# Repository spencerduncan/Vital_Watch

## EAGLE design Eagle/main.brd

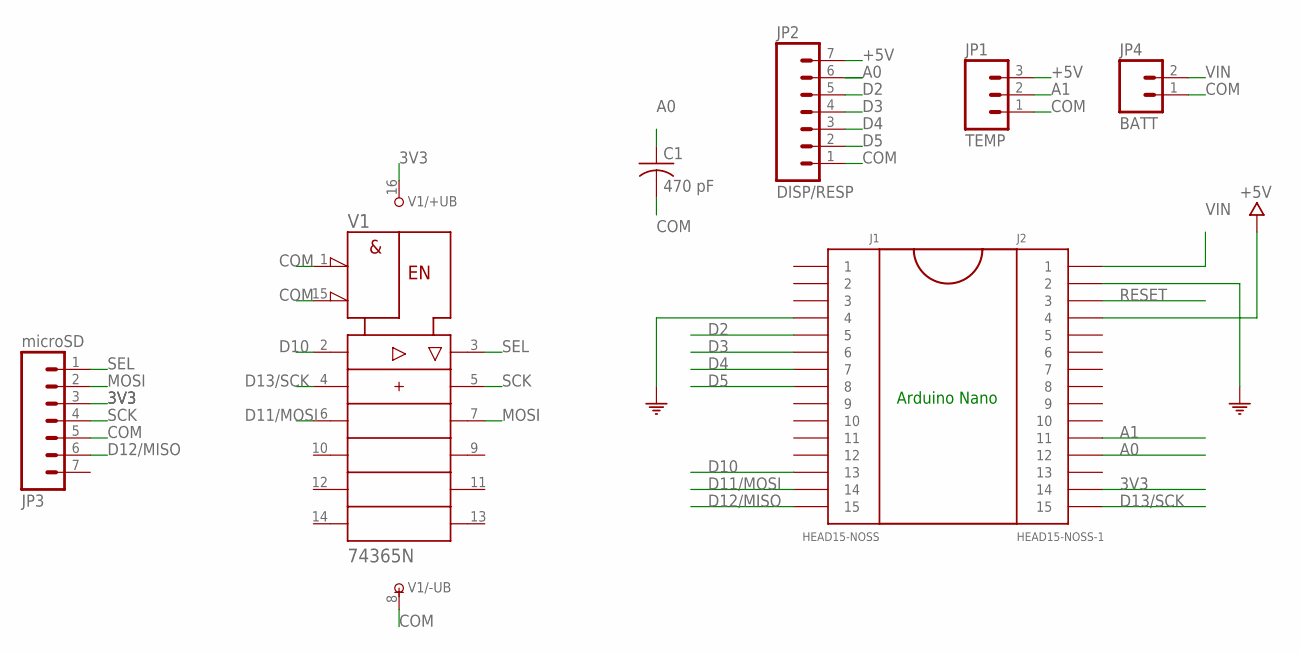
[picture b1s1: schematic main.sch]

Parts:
C1: 470 pF; C050-024X044
J1: HEAD15-NOSS
J2: HEAD15-NOSS-1
JP1: TEMP; 1X03
JP2: DISP/RESP; 1X07
JP3: microSD; 1X07
JP4: BATT; 1X02
V1: 74365N; DIL16

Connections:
3V3: J2.14, JP3.3, V1.16 (+UB)
+5V: J2.4, JP1.3, JP2.7
A0: C1.1, J2.12, JP2.6
A1: J2.11, JP1.2
COM: C1.2, J1.4, J2.2, JP1.1, JP2.1, JP3.5, JP4.1, V1.1 (!G1), V1.8 (-UB), V1.15 (!G2)
D2: J1.5, JP2.5
D3: J1.6, JP2.4
D4: J1.7, JP2.3
D5: J1.8, JP2.2
D10: J1.13, V1.2 (A1)
D11/MOSI: J1.14, V1.6 (A3)
D12/MISO: J1.15, JP3.6
D13/SCK: J2.15, V1.4 (A2)
MOSI: JP3.2, V1.7 (Y3)
RESET: J2.3
SCK: JP3.4, V1.5 (Y2)
SEL: JP3.1, V1.3 (Y1)
VIN: J2.1, JP4.2

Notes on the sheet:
Arduino Nano

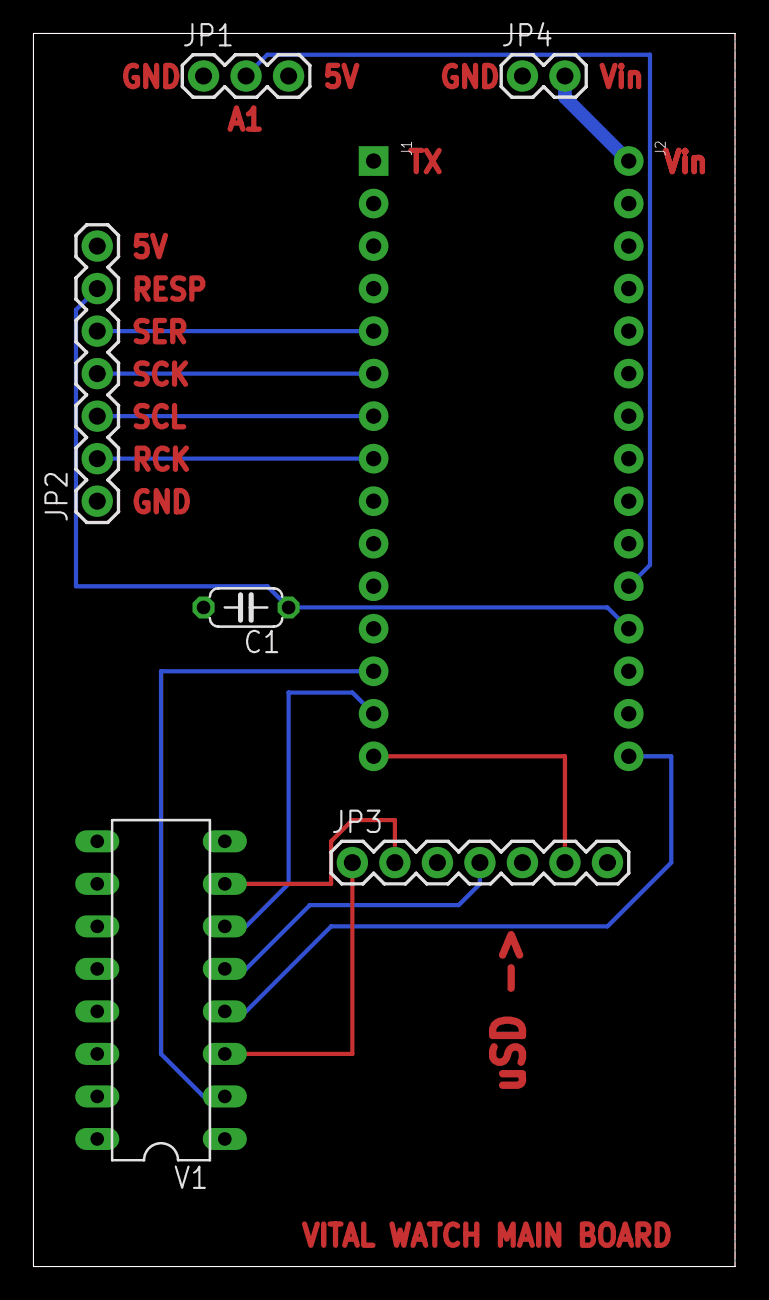
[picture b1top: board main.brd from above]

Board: 2 copper layers, 41.9 x 73.7 mm, 8 parts (0 on the bottom side), 17 nets.

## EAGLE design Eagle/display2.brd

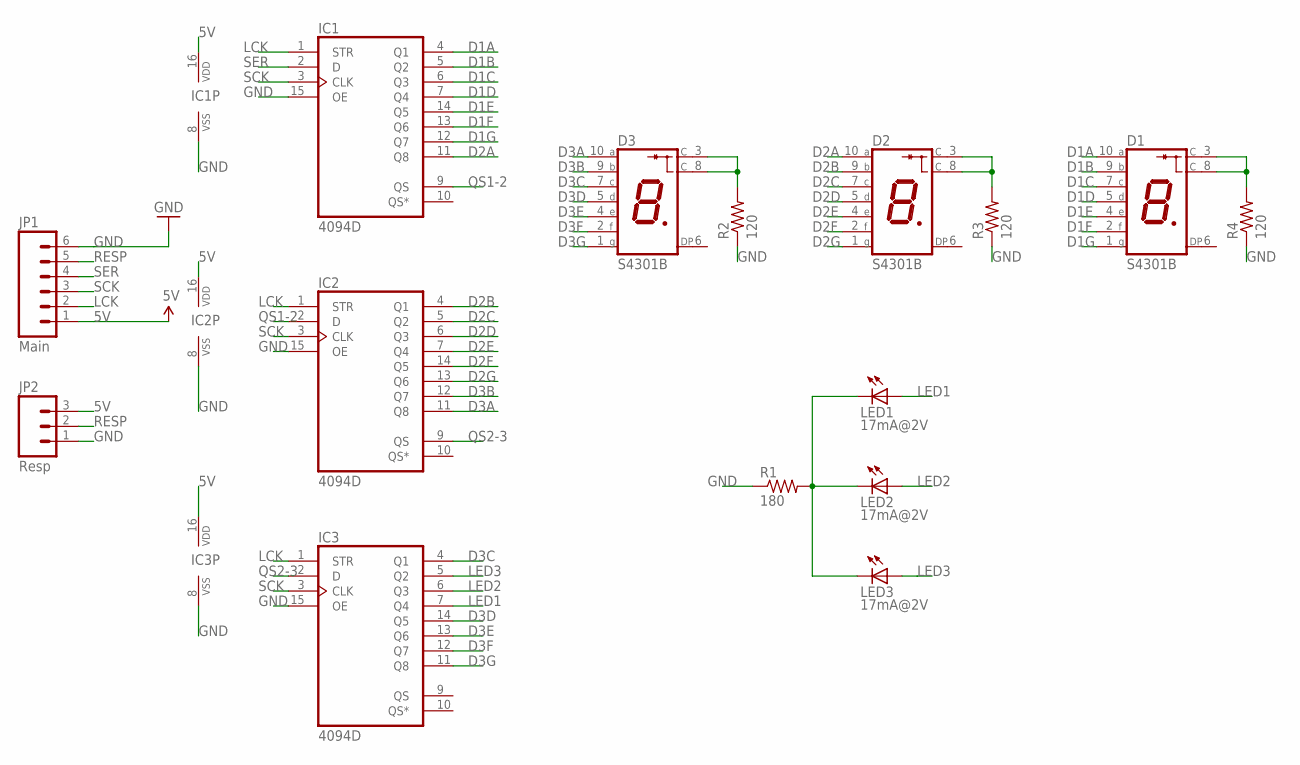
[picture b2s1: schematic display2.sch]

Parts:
D1, D2, D3: S4301B
IC1, IC2, IC3: 4094D; SO16
JP1: Main; 1X06
JP2: Resp; 1X03
LED1, LED2, LED3: 17mA@2V; LED3MM
R1: 180; 0204/5
R2, R3, R4: 120; 0204/5

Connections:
5V: IC1.16 (VDD), IC2.16 (VDD), IC3.16 (VDD), JP1.1, JP2.3
D1A: D1.10 (A), IC1.4 (Q1)
D1B: D1.9 (B), IC1.5 (Q2)
D1C: D1.7 (C), IC1.6 (Q3)
D1D: D1.5 (D), IC1.7 (Q4)
D1E: D1.4 (E), IC1.14 (Q5)
D1F: D1.2 (F), IC1.13 (Q6)
D1G: D1.1 (G), IC1.12 (Q7)
D2A: D2.10 (A), IC1.11 (Q8)
D2B: D2.9 (B), IC2.4 (Q1)
D2C: D2.7 (C), IC2.5 (Q2)
D2D: D2.5 (D), IC2.6 (Q3)
D2E: D2.4 (E), IC2.7 (Q4)
D2F: D2.2 (F), IC2.14 (Q5)
D2G: D2.1 (G), IC2.13 (Q6)
D3A: D3.10 (A), IC2.11 (Q8)
D3B: D3.9 (B), IC2.12 (Q7)
D3C: D3.7 (C), IC3.4 (Q1)
D3D: D3.5 (D), IC3.14 (Q5)
D3E: D3.4 (E), IC3.13 (Q6)
D3F: D3.2 (F), IC3.12 (Q7)
D3G: D3.1 (G), IC3.11 (Q8)
GND: IC1.8 (VSS), IC1.15 (OE), IC2.8 (VSS), IC2.15 (OE), IC3.8 (VSS), IC3.15 (OE), JP1.6, JP2.1, R1.1, R2.1, R3.1, R4.1
LCK: IC1.1 (STR), IC2.1 (STR), IC3.1 (STR), JP1.2
LED1: IC3.7 (Q4), LED1.A
LED2: IC3.6 (Q3), LED2.A
LED3: IC3.5 (Q2), LED3.A
unnamed: LED1.K (C), LED2.K (C), LED3.K (C), R1.2
unnamed: D3.3 (C), D3.8 (C), R2.2
unnamed: D2.3 (C), D2.8 (C), R3.2
unnamed: D1.3 (C), D1.8 (C), R4.2
QS1-2: IC1.9 (QS), IC2.2 (D)
QS2-3: IC2.9 (QS), IC3.2 (D)
RESP: JP1.5, JP2.2
SCK: IC1.3 (CLK), IC2.3 (CLK), IC3.3 (CLK), JP1.3
SER: IC1.2 (D), JP1.4

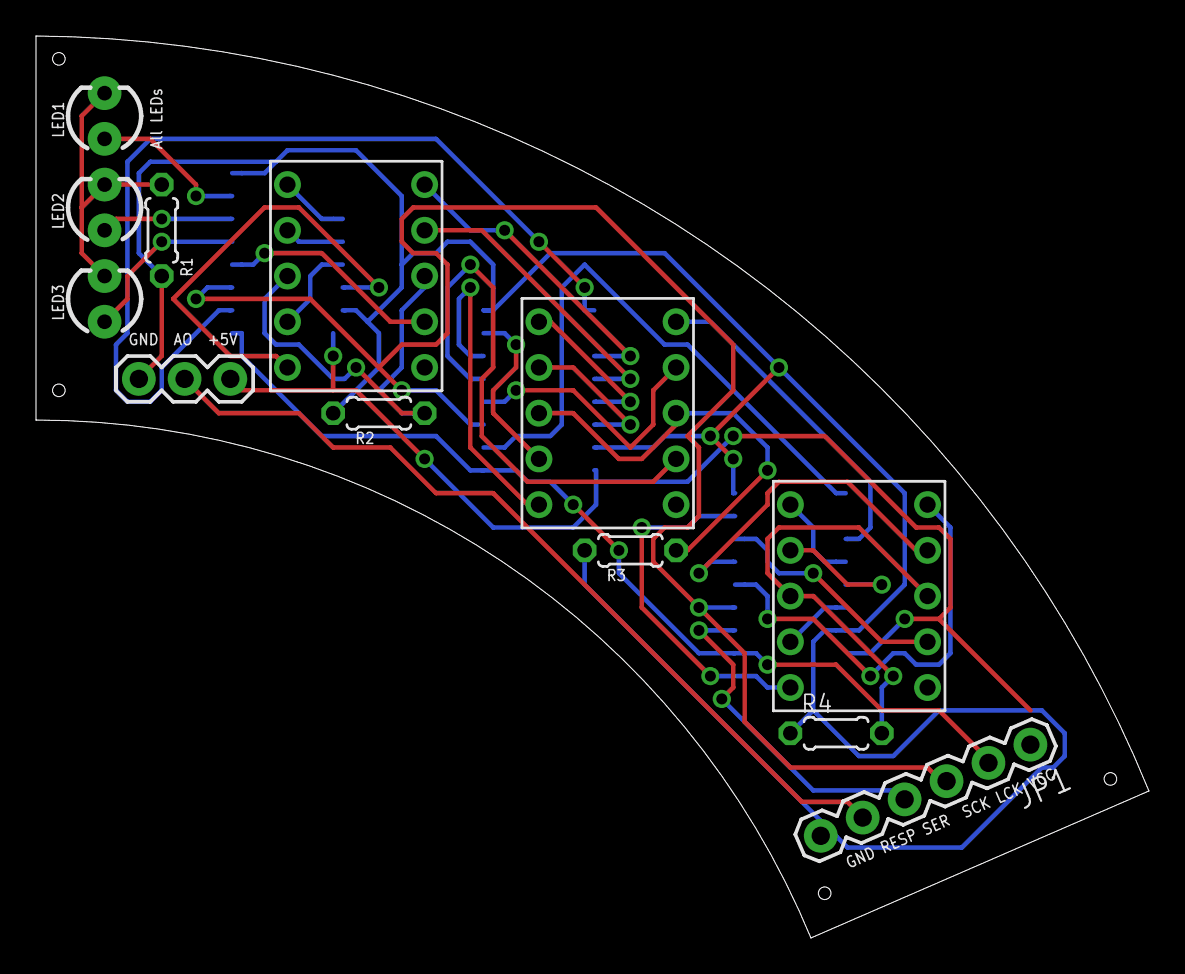
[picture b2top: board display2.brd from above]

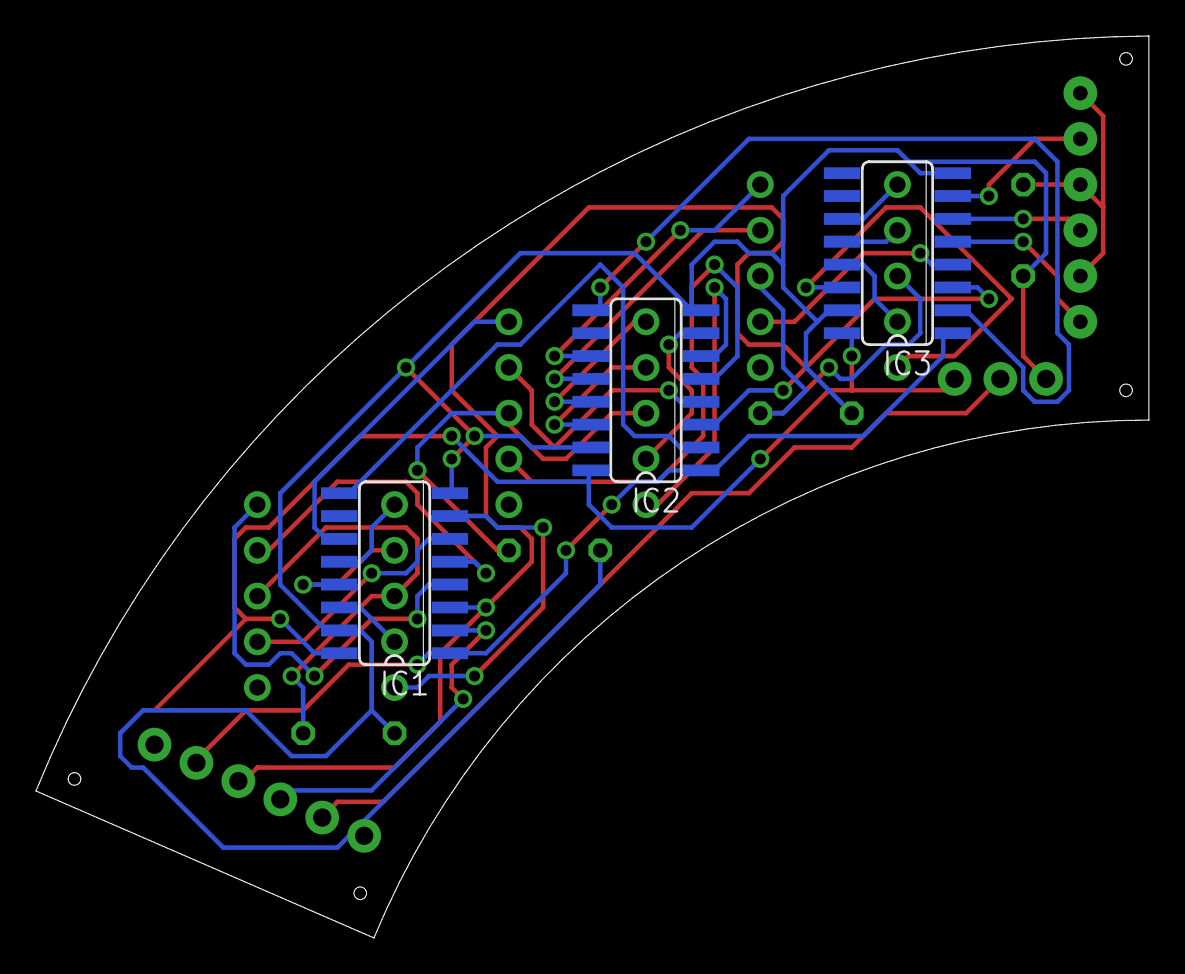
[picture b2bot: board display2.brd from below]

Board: 2 copper layers, 61.8 x 50.1 mm, 15 parts (3 on the bottom side), 36 nets.

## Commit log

2014-02-12 Commit From Archive
    Yea, for these were the days of salad and glory.

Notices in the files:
parts and their libraries:
SparkFun: Licensing: CC v3.0 Share-Alike You are welcome to use this library for commercial purposes.
